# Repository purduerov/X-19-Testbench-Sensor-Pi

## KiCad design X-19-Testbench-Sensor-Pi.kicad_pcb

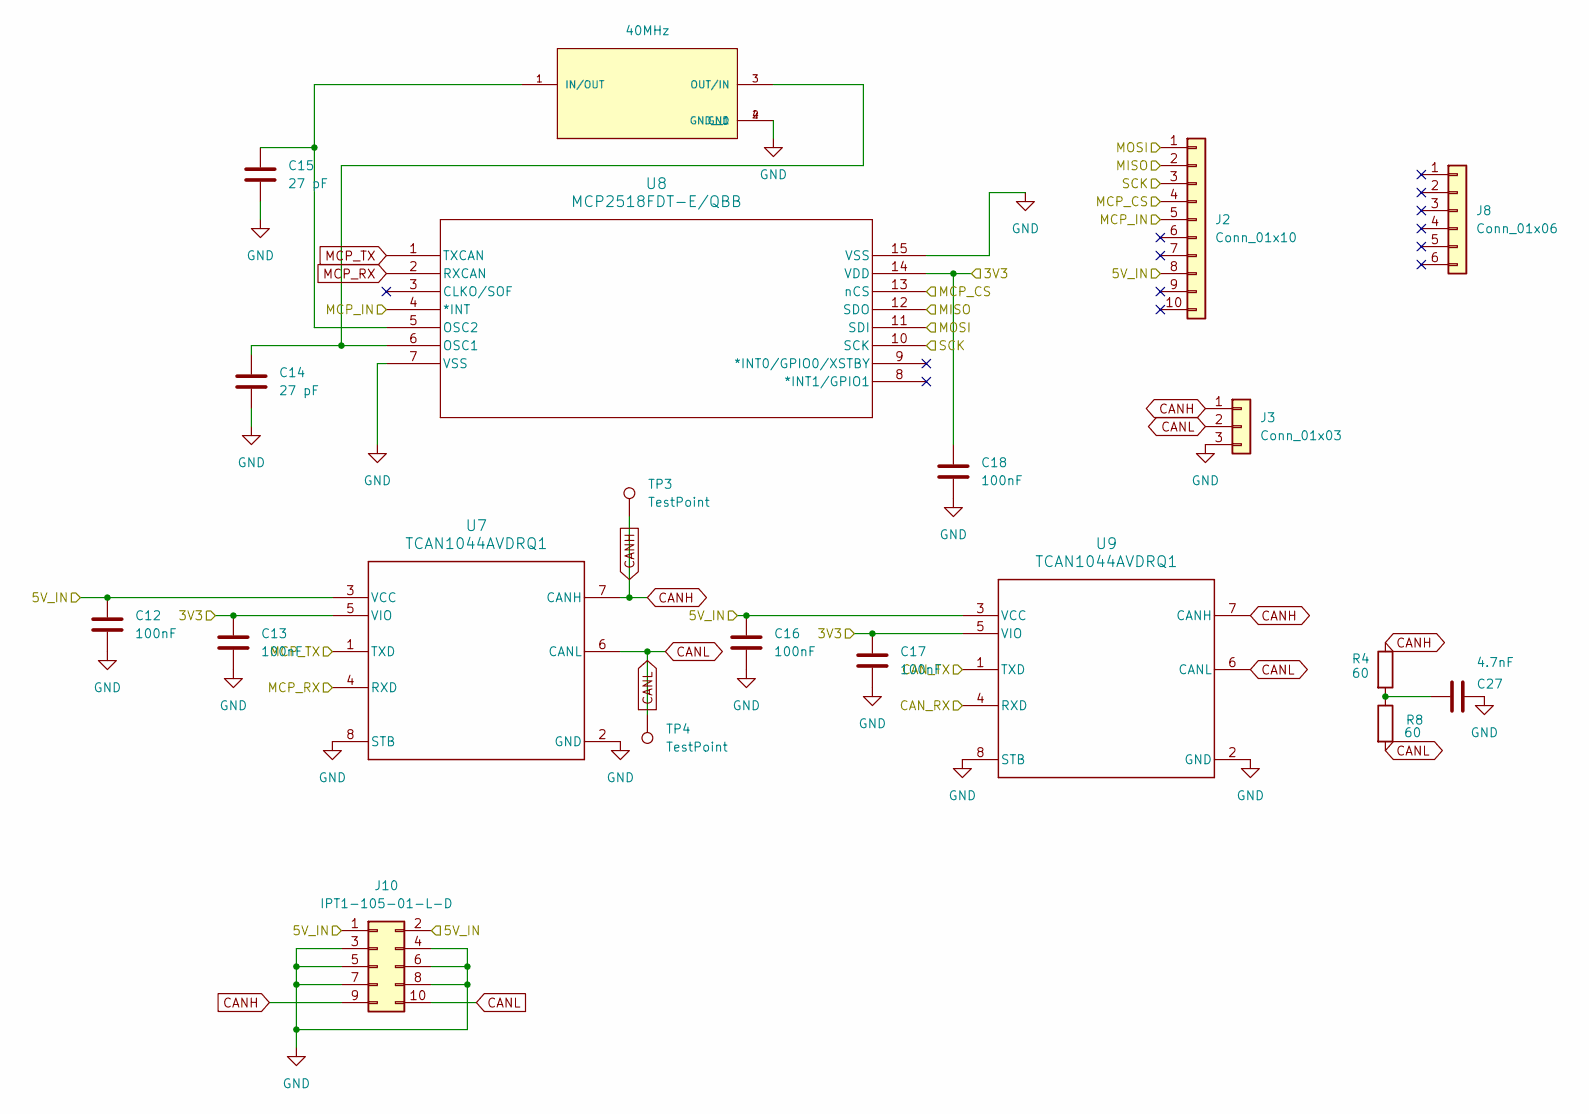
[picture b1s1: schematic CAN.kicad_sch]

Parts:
C12, C13, C16, C17, C18: 100nF; C_0201_0603Metric_Pad0.64x0.40mm_HandSolder
C14, C15: 27 pF; C_0201_0603Metric_Pad0.64x0.40mm_HandSolder
C27: 4.7nF; C_0201_0603Metric
J2: Conn_01x10; PinHeader_1x10_P2.54mm_Vertical
J3: Conn_01x03; TerminalBlock_MaiXu_MX126-5.0-03P_1x03_P5.00mm
J8: Conn_01x06; PinHeader_1x06_P2.54mm_Vertical
J10: IPT1-105-01-L-D; PinHeader_2x05_P2.54mm_Vertical
R4, R8: 60; R_0201_0603Metric_Pad0.64x0.40mm_HandSolder
TP3, TP4: TestPoint; TestPoint_Loop_D2.50mm_Drill1.0mm_LowProfile
U7, U9: TCAN1044AVDRQ1; D0008A-IPC_A; MPN TCAN1044D; DigiKey 296-TCAN1044DCT-ND
U8: MCP2518FDT-E/QBB; DFN-14-1EP_3x4.5mm_P0.65mm_EP1.65x4.25mm; MPN MCP2518FDT-E/QBB; DigiKey MCP2518FDT-E/QBBCT-ND
Y1: 40MHz; XTAL_ECS-400-18-33-JGN-TR; MPN ECS-400-18-33-JGN-TR; DigiKey XC1806TR-ND

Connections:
3V3: C13.1, C17.1, C18.1, U7.5 (VIO), U8.14 (VDD), U9.5 (VIO); also elsewhere on the board
5V_IN: C12.1, C16.1, J2.8, J10.1, J10.2, U7.3 (VCC), U9.3 (VCC); also elsewhere on the board
/CAN/CAN_RX: U9.4 (RXD); also elsewhere on the board
/CAN/CAN_TX: U9.1 (TXD); also elsewhere on the board
/CAN/MCP_CS: J2.4, U8.13 (nCS); also elsewhere on the board
/CAN/MCP_IN: J2.5, U8.4 (*INT); also elsewhere on the board
/CAN/MISO: J2.2, U8.12 (SDO); also elsewhere on the board
/CAN/MOSI: J2.1, U8.11 (SDI); also elsewhere on the board
/CAN/SCK: J2.3, U8.10 (SCK); also elsewhere on the board
CANH: J3.1, J10.9, R4.1, TP3.1 (1_1), U7.7 (CANH), U9.7 (CANH)
CANL: J3.2, J10.10, R8.2, TP4.1 (1_1), U7.6 (CANL), U9.6 (CANL)
GND: C12.2, C13.2, C14.2, C15.2, C16.2, C17.2, C18.2, C27.2, J3.3, J10.3, J10.4, J10.5, J10.6, J10.7, J10.8, U7.2 (GND), U7.8 (STB), U8.7 (VSS), U8.15 (VSS), U9.2 (GND), U9.8 (STB), Y1.2 (GND), Y1.4 (GND__1); also elsewhere on the board
MCP_RX: U7.4 (RXD), U8.2 (RXCAN)
MCP_TX: U7.1 (TXD), U8.1 (TXCAN)
unnamed: C27.1, R4.2, R8.1
unnamed: C14.1, U8.6 (OSC1), Y1.3 (OUT/IN)
unnamed: C15.1, U8.5 (OSC2), Y1.1 (IN/OUT)

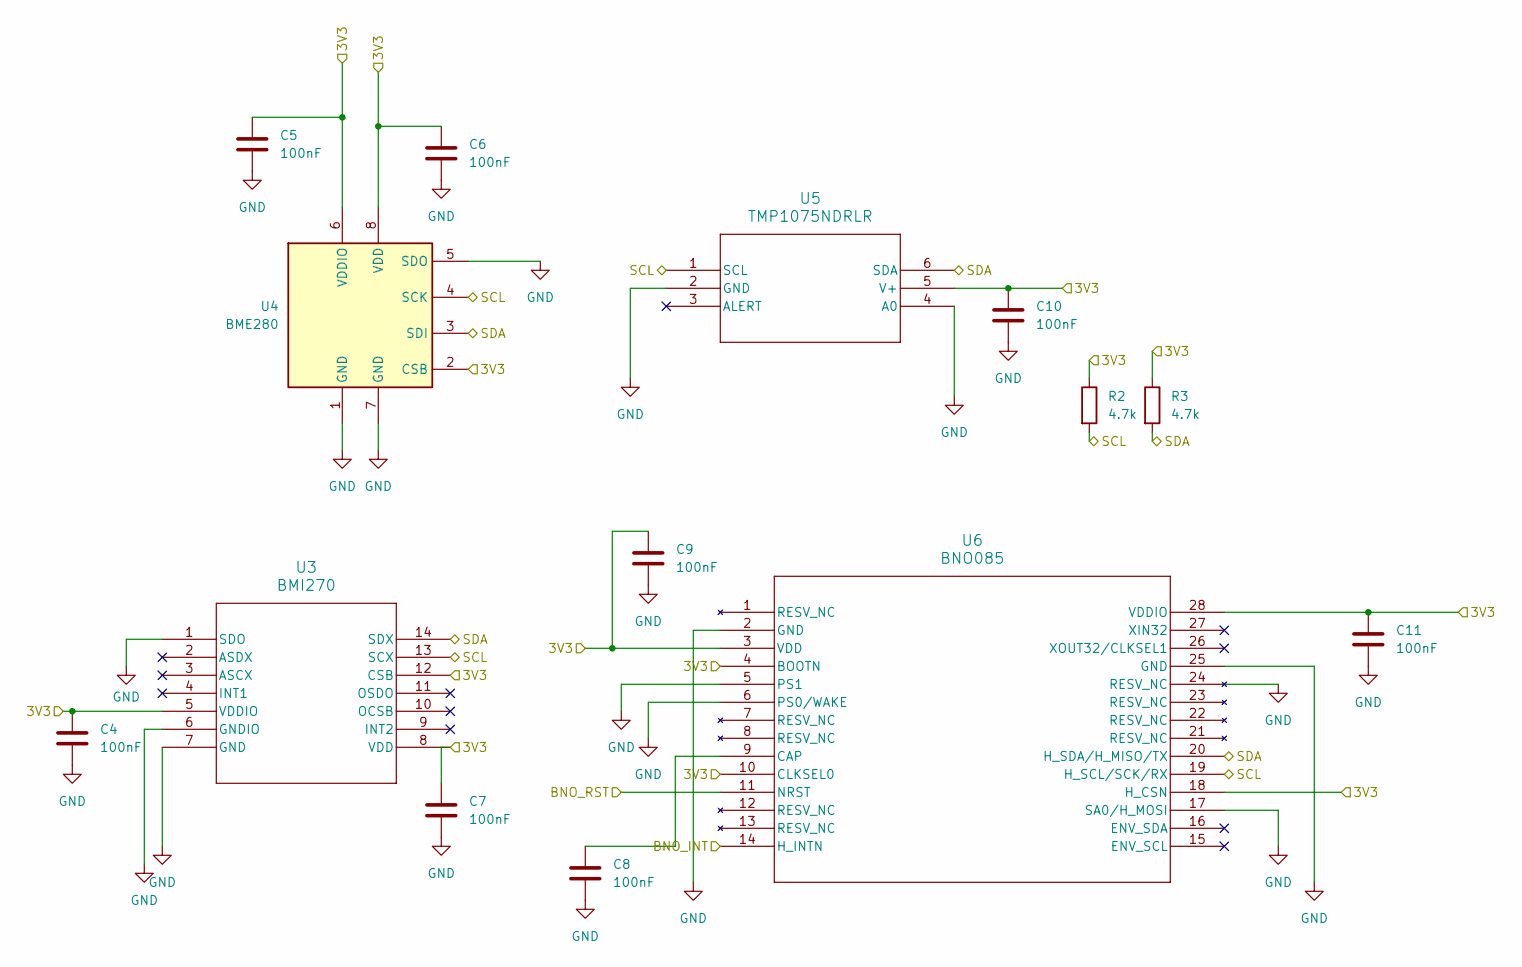
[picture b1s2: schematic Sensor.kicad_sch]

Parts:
C4, C5, C6, C7, C8, C9, C10, C11: 100nF; C_0201_0603Metric_Pad0.64x0.40mm_HandSolder
R2, R3: 4.7k; R_0201_0603Metric_Pad0.64x0.40mm_HandSolder
U3: BMI270; Bosch_LGA-14_3x2.5mm_P0.5mm; MPN BMI270; DigiKey 828-BMI270CT-ND
U4: BME280; Bosch_LGA-8_2.5x2.5mm_P0.65mm_ClockwisePinNumbering
U5: TMP1075NDRLR; SOT5X3-6_DRL_TEX; MPN TMP1075NDRLR; DigiKey 296-49272-1-ND
U6: BNO085; LGA-28_5.2x3.8mm_P0.5mm; MPN BNO085; DigiKey BNO085-ND

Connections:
3V3: C4.1, C5.1, C6.1, C7.1, C9.1, C10.1, C11.1, R2.1, R3.1, U3.5 (VDDIO), U3.8 (VDD), U3.12 (CSB), U4.2 (CSB), U4.6 (VDDIO), U4.8 (VDD), U5.5 (V+), U6.3 (VDD), U6.4 (BOOTN), U6.10 (CLKSEL0), U6.18 (H_CSN), U6.28 (VDDIO); also elsewhere on the board
/Compute/BNO_INT: U6.14 (H_INTN); also elsewhere on the board
/Compute/BNO_RST: U6.11 (NRST); also elsewhere on the board
/Compute/SCL: R2.2, U3.13 (SCX), U4.4 (SCK), U5.1 (SCL), U6.19 (H_SCL/SCK/RX); also elsewhere on the board
/Compute/SDA: R3.2, U3.14 (SDX), U4.3 (SDI), U5.6 (SDA), U6.20 (H_SDA/H_MISO/TX); also elsewhere on the board
GND: C4.2, C5.2, C6.2, C7.2, C8.2, C9.2, C10.2, C11.2, U3.1 (SDO), U3.6 (GNDIO), U3.7 (GND), U4.1 (GND), U4.5 (SDO), U4.7 (GND), U5.2 (GND), U5.4 (A0), U6.2 (GND), U6.5 (PS1), U6.6 (PS0/WAKE), U6.17 (SA0/H_MOSI), U6.24 (RESV_NC), U6.25 (GND); also elsewhere on the board
unnamed: C8.1, U6.9 (CAP)

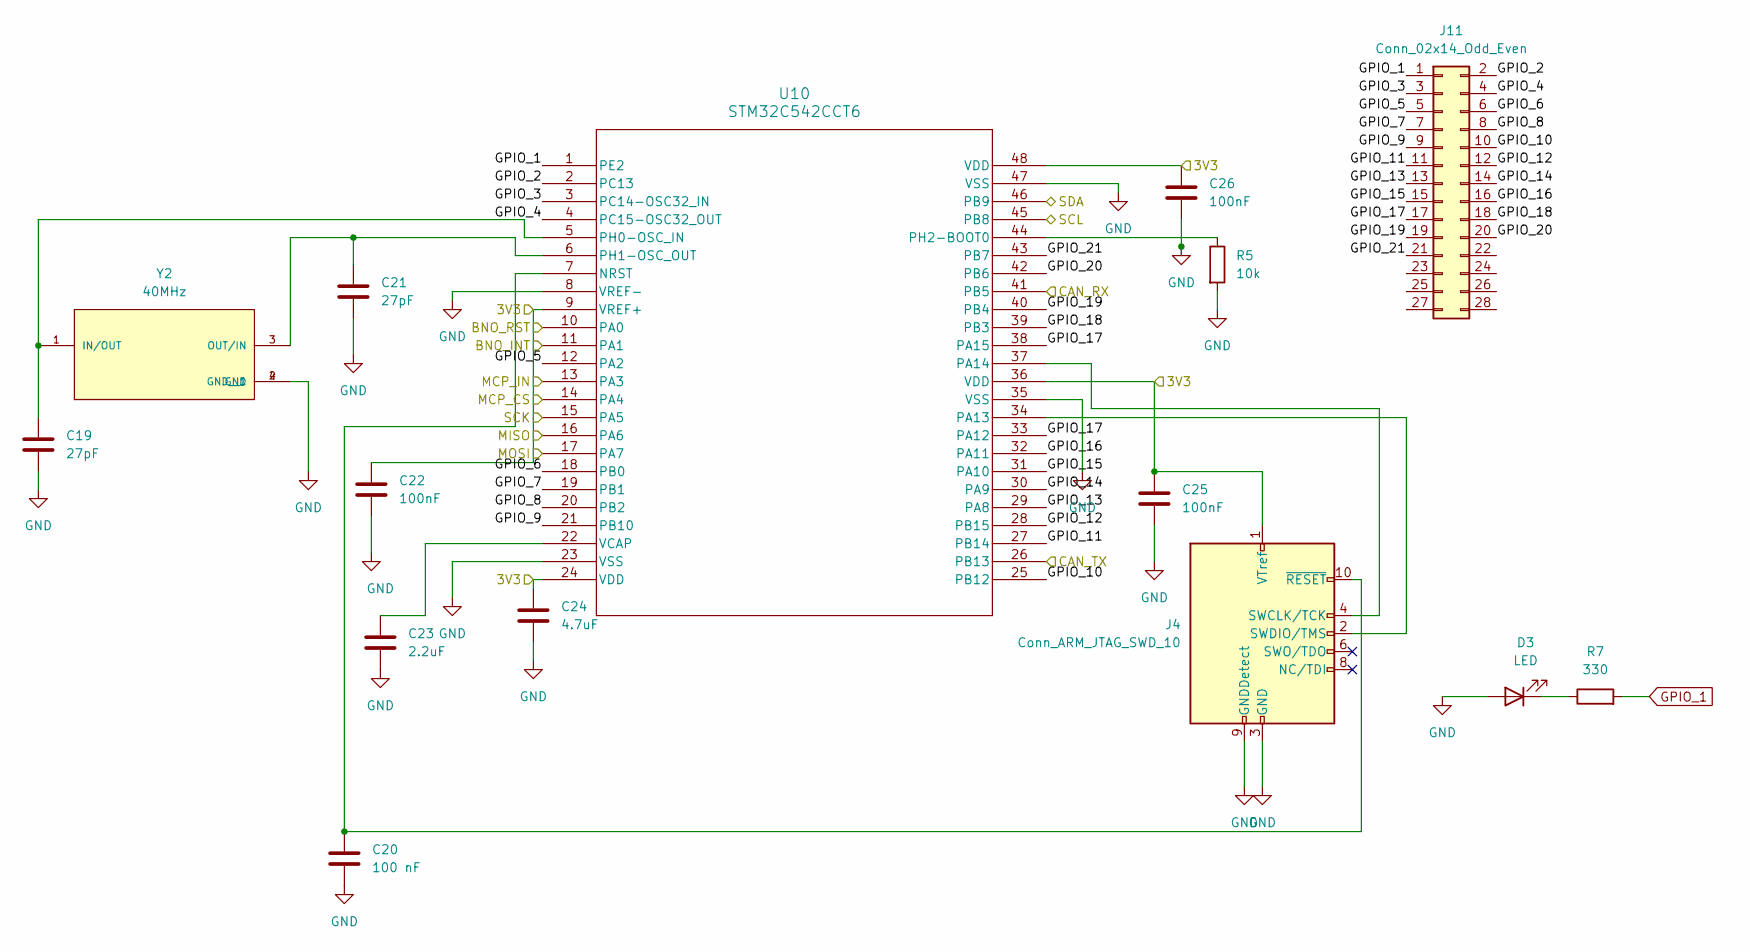
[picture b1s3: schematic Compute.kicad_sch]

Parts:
C19, C21: 27pF; C_0201_0603Metric_Pad0.64x0.40mm_HandSolder
C20: 100 nF; C_0201_0603Metric_Pad0.64x0.40mm_HandSolder
C22, C25, C26: 100nF; C_0201_0603Metric_Pad0.64x0.40mm_HandSolder
C23: 2.2uF; C_0201_0603Metric_Pad0.64x0.40mm_HandSolder
C24: 4.7uF; C_0201_0603Metric_Pad0.64x0.40mm_HandSolder
D3: LED; Fuse_0603_1608Metric_Pad1.05x0.95mm_HandSolder
J4: Conn_ARM_JTAG_SWD_10; PinHeader_2x05_P1.27mm_Vertical
J11: Conn_02x14_Odd_Even; PinHeader_2x14_P2.54mm_Vertical
R5: 10k; R_0201_0603Metric_Pad0.64x0.40mm_HandSolder
R7: 330; R_0201_0603Metric_Pad0.64x0.40mm_HandSolder
U10: STM32C542CCT6; LQFP48-7X7; MPN STM32C542CCT6
Y2: 40MHz; XTAL_ECS-400-18-33-JGN-TR; MPN ECS-400-18-33-JGN-TR; DigiKey XC1806TR-ND

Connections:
3V3: C22.1, C24.1, C25.1, C26.1, J4.1 (VTref), U10.9 (VREF+), U10.24 (VDD), U10.36 (VDD), U10.48 (VDD); also elsewhere on the board
/CAN/CAN_RX: U10.41 (PB5); also elsewhere on the board
/CAN/CAN_TX: U10.26 (PB13); also elsewhere on the board
/CAN/MCP_CS: U10.14 (PA4); also elsewhere on the board
/CAN/MCP_IN: U10.13 (PA3); also elsewhere on the board
/CAN/MISO: U10.16 (PA6); also elsewhere on the board
/CAN/MOSI: U10.17 (PA7); also elsewhere on the board
/CAN/SCK: U10.15 (PA5); also elsewhere on the board
/Compute/BNO_INT: U10.11 (PA1); also elsewhere on the board
/Compute/BNO_RST: U10.10 (PA0); also elsewhere on the board
/Compute/GPIO_2: J11.2, U10.2 (PC13)
/Compute/GPIO_3: J11.3, U10.3 (PC14-OSC32_IN)
/Compute/GPIO_4: J11.4, U10.4 (PC15-OSC32_OUT)
/Compute/GPIO_5: J11.5, U10.12 (PA2)
/Compute/GPIO_6: J11.6, U10.18 (PB0)
/Compute/GPIO_7: J11.7, U10.19 (PB1)
/Compute/GPIO_8: J11.8, U10.20 (PB2)
/Compute/GPIO_9: J11.9, U10.21 (PB10)
/Compute/GPIO_10: J11.10, U10.25 (PB12)
/Compute/GPIO_11: J11.11, U10.27 (PB14)
/Compute/GPIO_12: J11.12, U10.28 (PB15)
/Compute/GPIO_13: J11.13, U10.29 (PA8)
/Compute/GPIO_14: J11.14, U10.30 (PA9)
/Compute/GPIO_15: J11.15, U10.31 (PA10)
/Compute/GPIO_16: J11.16, U10.32 (PA11)
/Compute/GPIO_17: J11.17, U10.33 (PA12), U10.38 (PA15)
/Compute/GPIO_18: J11.18, U10.39 (PB3)
/Compute/GPIO_19: J11.19, U10.40 (PB4)
/Compute/GPIO_20: J11.20, U10.42 (PB6)
/Compute/GPIO_21: J11.21, U10.43 (PB7)
/Compute/SCL: U10.45 (PB8); also elsewhere on the board
/Compute/SDA: U10.46 (PB9); also elsewhere on the board
GND: C19.2, C20.2, C21.2, C22.2, C23.2, C24.2, C25.2, C26.2, D3.2 (A), J4.3 (GND), J4.5 (GND), J4.9 (GNDDetect), R5.2, U10.8 (VREF-), U10.23 (VSS), U10.35 (VSS), U10.47 (VSS), Y2.2 (GND), Y2.4 (GND__1); also elsewhere on the board
GPIO_1: J11.1, R7.2, U10.1 (PE2)
unnamed: D3.1 (K), R7.1
unnamed: J4.4 (SWCLK/TCK), U10.37 (PA14)
unnamed: J4.2 (SWDIO/TMS), U10.34 (PA13)
unnamed: C20.1, J4.10 (~RESET), U10.7 (NRST)
unnamed: C19.1, U10.5 (PH0-OSC_IN), Y2.1 (IN/OUT)
unnamed: C21.1, U10.6 (PH1-OSC_OUT), Y2.3 (OUT/IN)
unnamed: R5.1, U10.44 (PH2-BOOT0)
unnamed: C23.1, U10.22 (VCAP)

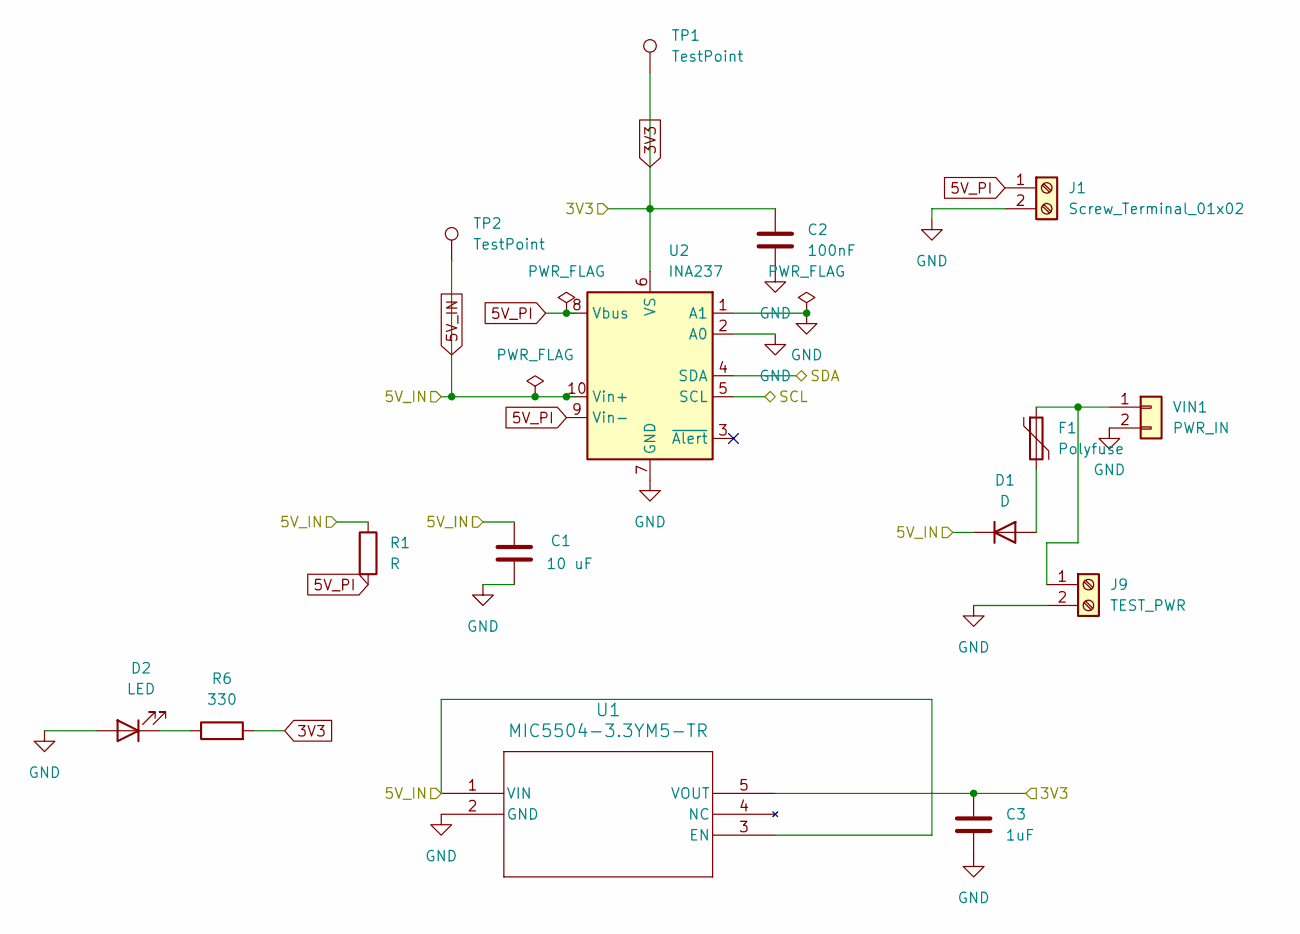
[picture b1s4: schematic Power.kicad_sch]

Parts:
C1: 10 uF; C_0201_0603Metric_Pad0.64x0.40mm_HandSolder
C2: 100nF; C_0201_0603Metric_Pad0.64x0.40mm_HandSolder
C3: 1uF; C_0201_0603Metric_Pad0.64x0.40mm_HandSolder
D1: D; Fuse_0603_1608Metric_Pad1.05x0.95mm_HandSolder
D2: LED; Fuse_0603_1608Metric_Pad1.05x0.95mm_HandSolder
F1: Polyfuse; Fuse_0603_1608Metric_Pad1.05x0.95mm_HandSolder
J1: Screw_Terminal_01x02; TerminalBlock_MaiXu_MX126-5.0-02P_1x02_P5.00mm
J9: TEST_PWR; TerminalBlock_4Ucon_1x02_P3.50mm_Vertical
R1: R; R_0201_0603Metric_Pad0.64x0.40mm_HandSolder
R6: 330; R_0201_0603Metric_Pad0.64x0.40mm_HandSolder
TP1, TP2: TestPoint; TestPoint_Loop_D2.50mm_Drill1.0mm_LowProfile
U1: MIC5504-3.3YM5-TR; SOT-23-5_MC_MCH; MPN MIC5504-3.3YM5-TR; DigiKey 576-4763-1-ND
U2: INA237; VSSOP_IDGSR_TEX
VIN1: PWR_IN; TerminalBlock_MaiXu_MX126-5.0-02P_1x02_P5.00mm

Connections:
3V3: C2.1, C3.1, R6.2, TP1.1 (1_1), U1.5 (VOUT), U2.6 (VS); also elsewhere on the board
5V_IN: C1.1, D1.1 (K), R1.1, TP2.1 (1_1), U1.1 (VIN), U1.3 (EN), U2.10 (Vin+); also elsewhere on the board
5V_PI: J1.1, R1.2, U2.8 (Vbus), U2.9 (Vin-)
/Compute/SCL: U2.5 (SCL); also elsewhere on the board
/Compute/SDA: U2.4 (SDA); also elsewhere on the board
GND: C1.2, C2.2, C3.2, D2.2 (A), J1.2, J9.2, U1.2 (GND), U2.1 (A1), U2.2 (A0), U2.7 (GND), VIN1.2; also elsewhere on the board
unnamed: D1.2 (A), F1.2
unnamed: D2.1 (K), R6.1
unnamed: F1.1, J9.1, VIN1.1

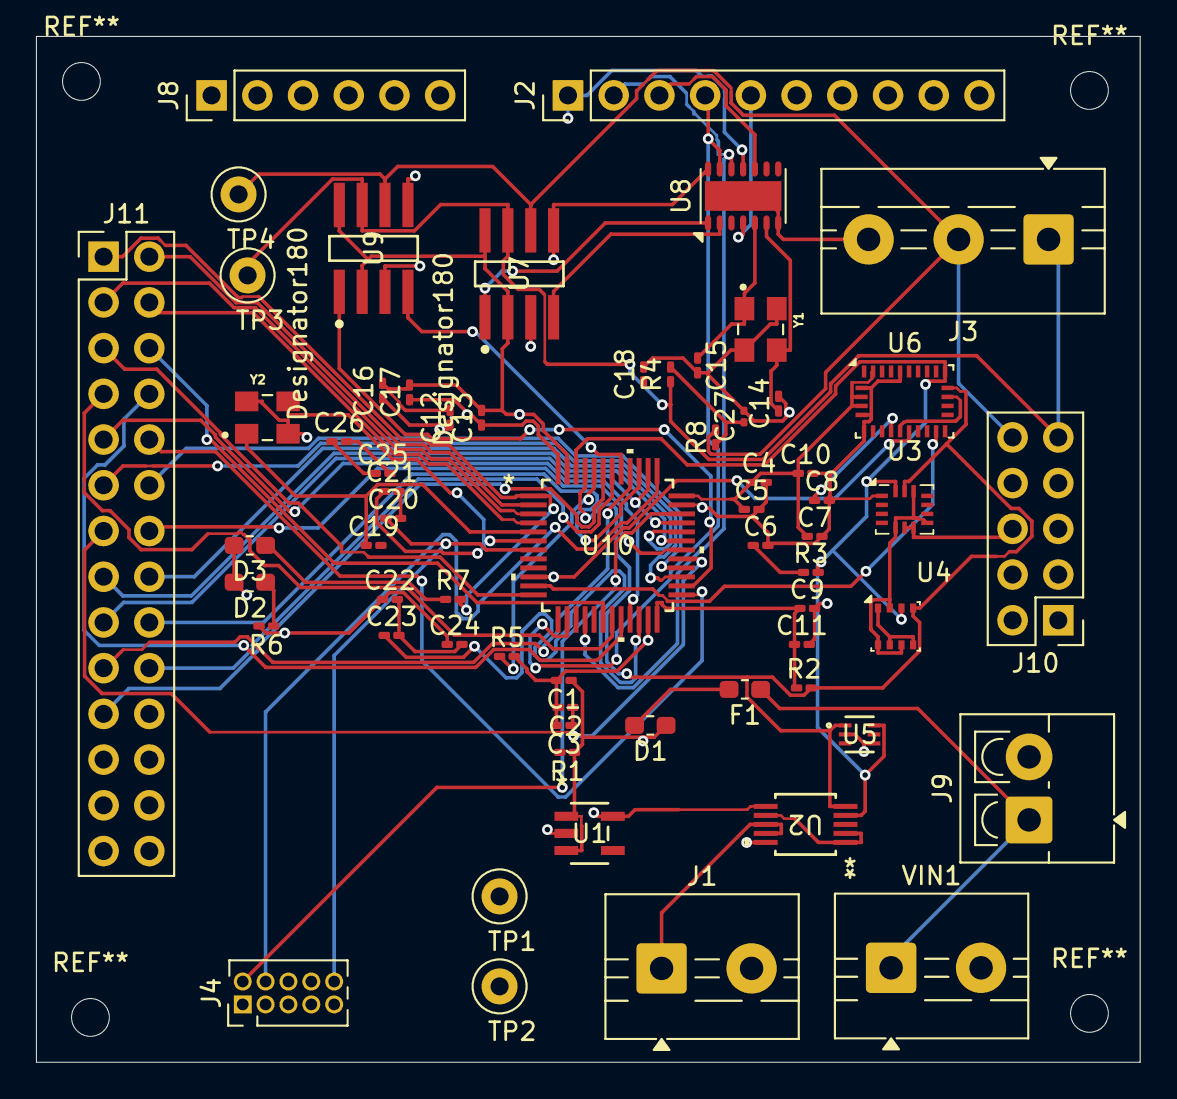
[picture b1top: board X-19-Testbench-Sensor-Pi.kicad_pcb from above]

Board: 4 copper layers, 61.3 x 57.0 mm, 64 parts (0 on the bottom side), 55 nets.
